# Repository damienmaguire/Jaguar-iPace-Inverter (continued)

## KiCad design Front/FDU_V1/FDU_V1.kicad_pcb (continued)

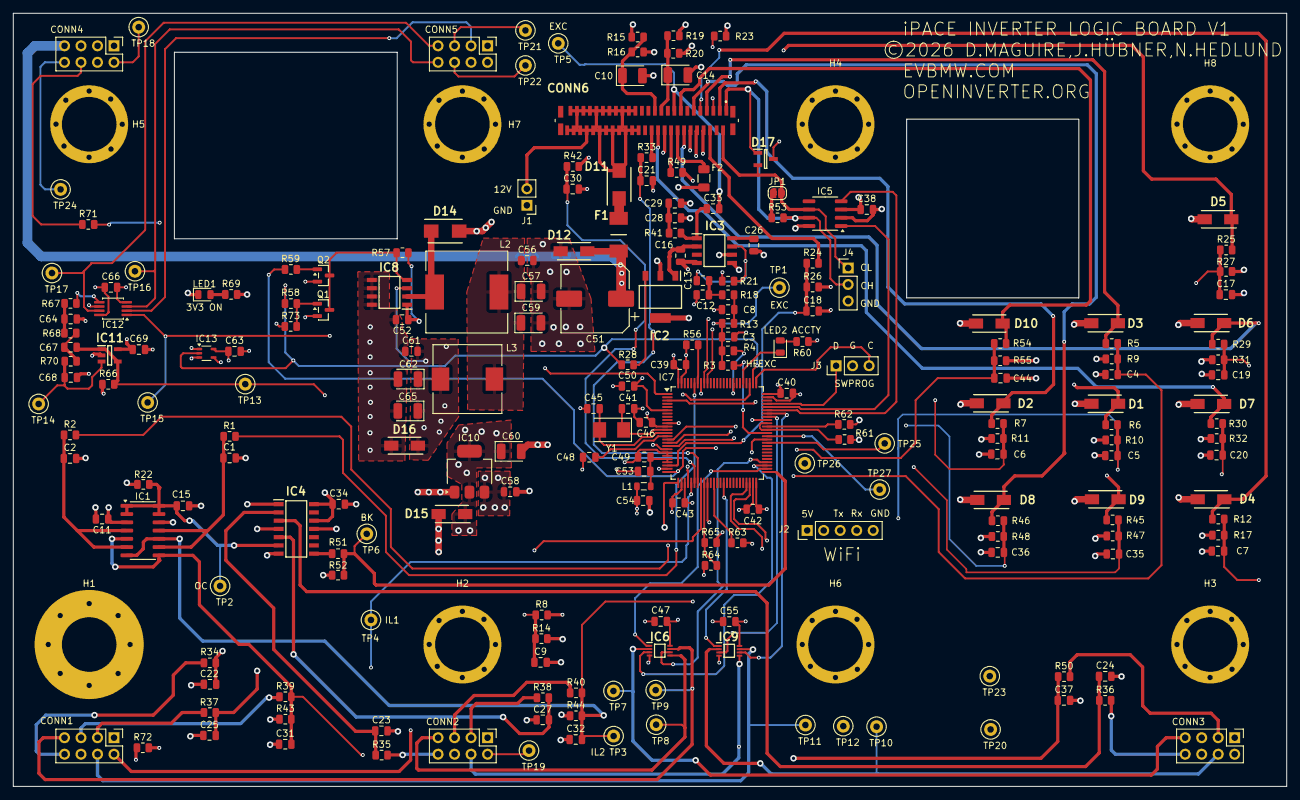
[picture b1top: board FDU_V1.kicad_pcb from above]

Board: 6 copper layers, 196.0 x 119.0 mm, 227 parts (0 on the bottom side), 137 nets.

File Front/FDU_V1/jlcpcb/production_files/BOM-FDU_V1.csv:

Comment,Designator,Footprint,LCSC,Quantity
0.1uF,"C11,C34,C38,C39,C40,C42,C43,C46,C47,C48,C49,C50,C53,C55,C63,C66,C69",C_0805_2012Metric,C126469,17
0R,R49,R_0805_2012Metric,C17477,1
100R,"R71,R72",R_0805_2012Metric,C17408,2
100uF 6.3V,"C10,C14,C57,C59,C60,C62,C65",CP_EIA-3528-15_AVX-H,C7195,7
10K,"R1,R17,R2,R21,R27,R33,R42,R56,R63,R66,R73",R_0805_2012Metric,C17414,10
10R,R41,R_0805_2012Metric,C17415,1
10nF,"C15,C22,C23,C24,C25,C27,C37",C_0805_2012Metric,C1710,7
10uF,"C16,C33,C58",C_0805_2012Metric,C15850,3
10uH 0805,L1,L_0805_2012Metric,C88172,1
1206L050/24WR,F2,Fuse_1206_3216Metric,C2154056,1
120R,R53,R_0805_2012Metric,C17437,1
150pF,C68,C_0805_2012Metric,C107111,1
1K,"R58,R59",R_0805_2012Metric,C149504,2
1K,"R28,R45,R46,R47,R48,R51,R61,R62,R67",R_0805_2012Metric,C17513,8
1K2,"R12,R23,R24,R25,R8",R_0805_2012Metric,C114526,5
1K5,"R10,R11,R31,R32,R55,R9",R_0805_2012Metric,C114555,6
1K8,"R13,R18",R_0805_2012Metric,C114222,2
1N5,C64,C_0805_2012Metric,C1717,1
1nF,"C21,C30,C31,C32,C61",C_0805_2012Metric,C94121,5
1uF,"C1,C17,C18,C19,C2,C20,C26,C35,C36,C4,C5,C52,C54,C56,C6,C7,C9",C_0805_2012Metric,C215803,17
1uF 25V,C44,C_0805_2012Metric,C116352,1
220R,"R15,R16,R19,R20",R_0805_2012Metric,C17557,4
22nF,"C12,C13,C28,C29,C3,C8",C_0805_2012Metric,C1729,6
27K,R57,R_0805_2012Metric,C17593,1
27pF,"C41,C45",C_0805_2012Metric,C1808,2
2K,R52,R_0805_2012Metric,C17604,1
2K2,"R14,R22,R26",R_0805_2012Metric,C114561,3
2K6,"R43,R44",R_0805_2012Metric,C144568,2
330Pf,C67,C_0805_2012Metric,C107116,1
3K9,"R3,R64",R_0805_2012Metric,C114221,2
LEDS,"LED1,LED2",LED_0805_2012Metric,C84256,2
3uH,L3,L_10.4x10.4_H4.8,C31964,1
470uF 25V,C51,CP_Elec_10x10,C46550466,1
47K,R65,R_0805_2012Metric,C17713,1
4K7,"R29,R30,R5,R54,R6,R7",R_0805_2012Metric,C60816,6
560R,"R34,R35,R36,R37,R38,R50",R_0805_2012Metric,C28636,6
5K1,R70,R_0805_2012Metric,C84375,1
680R,"R60,R69",R_0805_2012Metric,C17798,2
68uH,L2,L_12x12mm_H8mm,C9907,1
6K2,"R39,R40",R_0805_2012Metric,C114535,2
6K8,R68,R_0805_2012Metric,C137409,1
8MHz,Y1,Crystal_SMD_5032-2Pin_5.0x3.2mm,C115962,1
AMS1117-3.3,IC10,SOT-223-3_TabPin2,C6186,1
CD74HC30M96,IC4,SOIC127P600X175-14N,C6540,1
ESDCAN01-2BLY,D17,SOT95P255X150-3N,C53340814,1
FH12-50S-0.5SVA_54_,CONN6,FH1250S05SVA54,C597991,1
JFC2410-0500TS,F1,FUSC6126X280N,C136377,1
LM2901,IC1,SOIC-14_3.9x8.7mm_P1.27mm,C7932,1
MCP6291T-E_OT,IC11,SOT95P280X145-5N,C145575,1
MMBT3904,"Q1,Q2",SOT-23,C20526,2
NCV8452STT3G,IC2,SOT230P700X180-4N,C477982,1
SMAJ18CA,"D10,D12",DIONM5127X229N,C10768,2
SMAJ5.0A,"D1,D15,D2,D3,D4,D5,D6,D7,D8,D9",DIOM5127X229N,C83329,10
SMAJ7.0A,D16,DIOM5026X229N,C138782,1
SN65HVD230,IC5,SOIC-8_3.9x4.9mm_P1.27mm,C12084,1
SN74LVC1G125DCK,IC13,Texas_R-PDSO-G5_DCK-5,C7833,1
SN74LVC3G04DCUR,IC9,SOP50P310X90-8N,C153799,1
SN74LVC3G17DCTR,"IC12,IC6",MSOP-8_3x3mm_P0.65mm,C18213,2
SS54B,"D11,D14",DIOM5336X244N,C32513,2
STM32F103VCTx,IC7,LQFP-100_14x14mm_P0.5mm,C53327627,1
TDA2822D,IC3,SOIC127P600X175-8N,C668663,1
XL1509-5.0E1,IC8,SOIC127P600X175-8N,C61063,1

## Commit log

2026-03-27 Add V1 board
2026-03-27 Add pdfs
2026-03-28 Update design as per order
